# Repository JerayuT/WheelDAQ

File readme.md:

Wheel DAQ Design

Wheel Daughter Boards are in charge of all the sensors near or at the wheels of the car. This goal is to make a printed circuit board that is able to interface with all these sensors, and then be able to translate them and send the data over CAN. Each board will have the following components listed below for a total of 4 boards (each wheel).

Components:<br>
- ESP-32 dev-kit C
- Can Transceiver 
- 26-pin connector
- WheelBreak Sensor
- Break Temperature
- Boost Converter
- RR Op-Amp

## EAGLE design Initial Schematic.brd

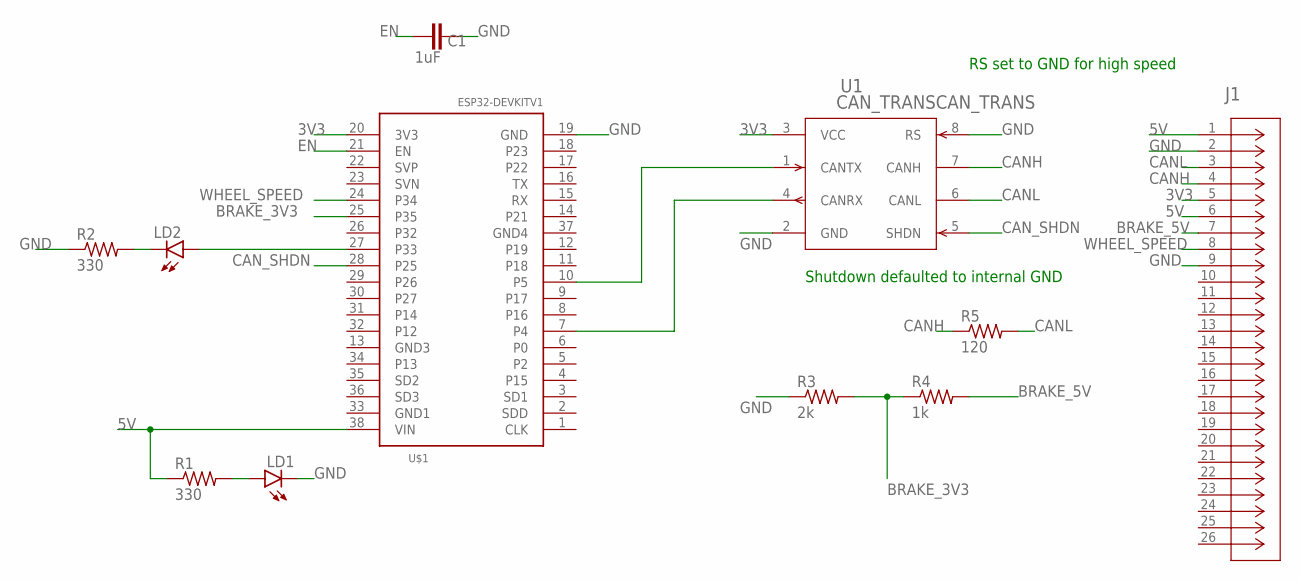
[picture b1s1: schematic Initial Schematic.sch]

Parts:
C1: 1uF; C1206
J1: CONNECTOR; CONN26_9-6437287-8_TEC
LD1, LD2: PL006-WCR21; SOT23
R1, R2: 330; R1206
R3: 2k; R1206
R4: 1k; R1206
R5: 120; R1206
U1: CAN_TRANSCAN_TRANS; MAX3051ESA+
U$1: ESP32DEVKITV1; ESP32-DEVKITV1

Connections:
3V3: J1.5, U1.3 (VCC), U$1.20 (3V3)
5V: J1.1, J1.6, R1.1, U$1.38 (VIN)
BRAKE_3V3: R3.2, R4.1, U$1.25 (P35)
BRAKE_5V: J1.7, R4.2
CANH: J1.4, R5.1, U1.7 (CANH)
CANL: J1.3, R5.2, U1.6 (CANL)
CAN_SHDN: U1.5 (SHDN), U$1.28 (P25)
EN: C1.2, U$1.21 (EN)
GND: C1.1, J1.2, J1.9, LD1.1 (C), R2.1, R3.1, U1.2 (GND), U1.8 (RS), U$1.19 (GND)
unnamed: U1.1 (CANTX), U$1.10 (P5)
unnamed: LD1.3 (A), R1.2
unnamed: U1.4 (CANRX), U$1.7 (P4)
unnamed: LD2.3 (A), U$1.27 (P33)
unnamed: LD2.1 (C), R2.2
WHEEL_SPEED: J1.8, U$1.24 (P34)

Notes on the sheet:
RS set to GND for high speed
Shutdown defaulted to internal GND

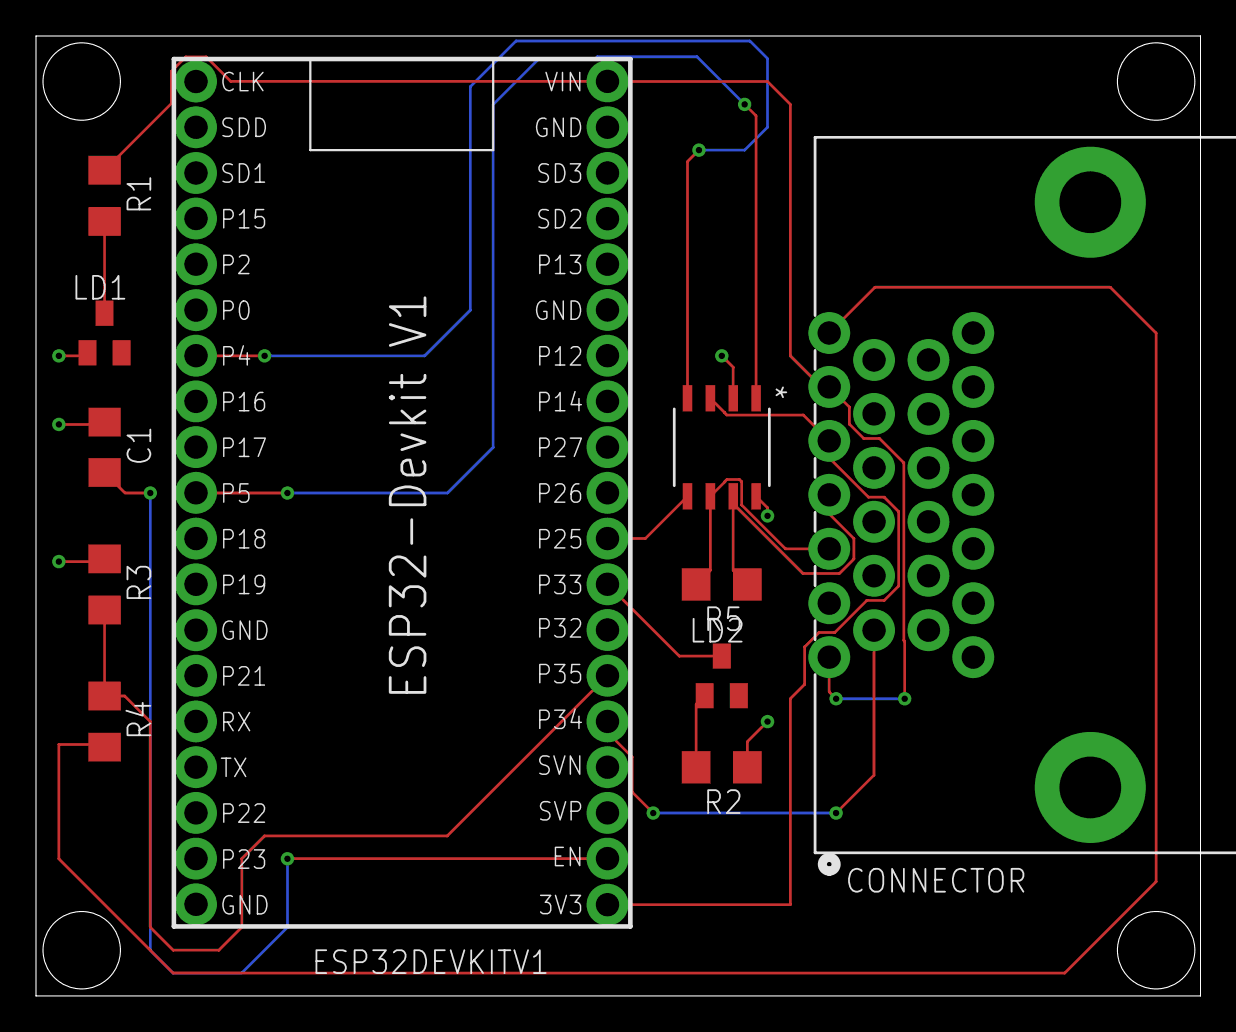
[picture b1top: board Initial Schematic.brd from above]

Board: 2 copper layers, 64.7 x 53.3 mm, 11 parts (0 on the bottom side), 15 nets.

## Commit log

2022-10-04 Initial Schematic
2022-10-13 Finished schematic
2022-10-15 Got the sensor to output some stuff
2022-11-15 Removed Boost
2022-12-23 Created PCB Layout
2023-01-05 Revised layout
2023-01-05 Layout v3
2023-01-05 Layout v4

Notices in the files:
parts and their libraries:
COPYRIGHT: Copyright (C) 2022 Ultra Librarian. All rights reserved.
